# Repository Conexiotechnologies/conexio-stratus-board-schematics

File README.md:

# Conexio Stratus Cellular Board Design
Here you will find the schematic designs for the Conexio Stratus IoT dev kit based on nRF91xx series and the associated shields and the expansion dock.
A detailed description of the pin mapping can be found in each specific board directory.

## nRF9151 Conexio Stratus Pro Series

**Conexio Stratus Pro** is a tiny-yet-powerful development kit for creating cellular-connected electronic projects and products. Powered by the cutting-edge nRF9161 cellular modem from Nordic Semiconductor, Stratus Pro offers unparalleled versatility, reliability, and ease of use, making it the go-to solution for IoT developers worldwide. It is a battery-operated platform, making it ideal for prototyping cellular IoT systems, such as asset tracking, environmental monitoring, smart metering, and even industrial automation.

With LTE-M, NB-IoT, and GPS connectivity packed into a compact form factor, Stratus Pro ensures your devices stay connected in any environment. It enables real-time data transmission and location tracking with minimal power consumption. Future-proof your IoT projects with DECT NR+ readiness, ensuring compatibility with emerging cellular standards for enhanced performance and longevity.

## Built-In Battery Charging, Monitoring and Energy-Harvesting

Thanks to the nPM1300 PMIC and fuel gauge, you can remotely monitor your Stratus Pro’s battery vitals and charging status. Stratus Pro also has built-in charging circuitry that makes it easier to connect to and recharge the Li-Po battery, creating fully energy-autonomous applications.

## Conexio Stratus Pro nRF9151 Pinouts

## Features & Specifications

**MCU**: Nordic nRF9151 Microcontroller 
- ARM Cortex-M33 with 1 MB Flash
- 256 kB RAM
- Pre-programmed MCUBoot bootloader

**Modem**
- Transceiver and baseband
- 3GPP LTE release 14 LTE-M/NB-IoT support
- DECT NR+ ready
- GPS/GNSS receiver
- RF Transceiver for global coverage supporting bands:
- B1, B2, B3, B4, B5, B8, B12, B13, B17, B18, B19, B20, B25, B26, B28, B65 (new), B66, and B85 (new)
- Supports 4FF Nano SIM, optional eSIM, or software SIM

**Included cellular Data**
- 500 MB of cellular data
- 250 SMS messages
- Valid for 10 years, can be reloaded or moved to a new plan
- Service available in 100+ countries (LTE + NB-IoT)

**Power Management IC: Nordic nPM1300**
- 800 mA battery charger
- Dual 200 mA buck DC/DC regulator
- Charging IC: Texas Instruments BQ25185
- Charge inputs: 3 V to 18 V
- Supports Li-ion, Li-Poly, and LiFePO4 battery chemistries

**External Storage**
- 16 KBit I2C EEPROM memory (24CW160T)

**Power**
- Operating range 1.8 to 5.5 V
- External LiPo battery connection (2 Pin JST type)
- Maximum output current: 800 mA
- Output voltages (via headers): 1.8 V, 3.3 V, 5 V (VUSB), VBAT
- SPDT slide switch for turning Stratus Pro on or off
- Quiescent current of entire board < 9 μA

**Onboard sensors**
- Battery fuel gauge enabled by nPM1300
- STMicroelectronics LIS2DH MEMS high-performance 3-axis accelerometer

**I/O**
- USB Type-C, for USB-to-Serial, DFU, and application firmware programming and debugging or battery charging
- 1 x U.FL for LTE-M/NB-IoT antenna
- 1 x U.FL for passive GPS antenna
- Total I/O pinouts: 36
- User I/O: Feather-compatible header, 28 programmable GPIO pins, 2 push buttons (1 reset, 1 programmable), 1 programmable LED
- QWIIC connector for external peripherals
- Supports J-Link and CMSIS-DAP-based programmers
- Onboard 10-pin 0.05 " (1.27 mm) mini SWD/JTAG pin connector

**Size**
- 66.04 mm x 25.40 mm

## Stratus Pro Expansion Dock

Start your product development with our Expansion Dock for Stratus Pro fast and easy. The Expansion Dock offers two QWIIC connectors, two Grove sockets, a mikroBUS™ socket, an nRF7002 Expansion board socket to add Wi-Fi location capabilities, and a SeeedStudio Xiao socket allowing you to create various wireless applications with one host board. It can't get any better than this., working with a Stratus shield requires no soldering and minimal wiring. Just plug the sensors, actuators, or displays into this shield via the standard cables, and focus on coding and application creation.

## Features & Specifications

- 2 x Stratus Pro nRF9151/nRF9161 header sockets.
- 1 x nRF7002EB socket.
- 1 x SeeedStudio Xiao socket.
- 1 x mikro BUS: add-on board standard from Mikroe, allowing connection to over 800+ click boards.
- 2 x Sparkfun Qwiic connector: SparkFun's Qwiic Connect System, allowing to connect over 100+ Qwiic products.
- 2 x Grove I2C connector: Grove is a modular, standardized connector prototyping system by Seeedstudio.
- 1 x 2 Pin JST connector for plugging the solar panel input.
- 1 x 2 Pin JST connector for plugging the lipo battery.
- 1 x Power switch

## Purchase

Conexio Stratus devices and accessories can be purchased directly from our [online store](https://conexiotech.com/shop/).

Please contact [info@conexiotech.com](mailto:info@conexiotech.com) if you would like to arrange help with your manufacturing and custom PCB design based on Stratus Pro platform. 

Copyright (c) 2025 Conexio Technologies, Inc.

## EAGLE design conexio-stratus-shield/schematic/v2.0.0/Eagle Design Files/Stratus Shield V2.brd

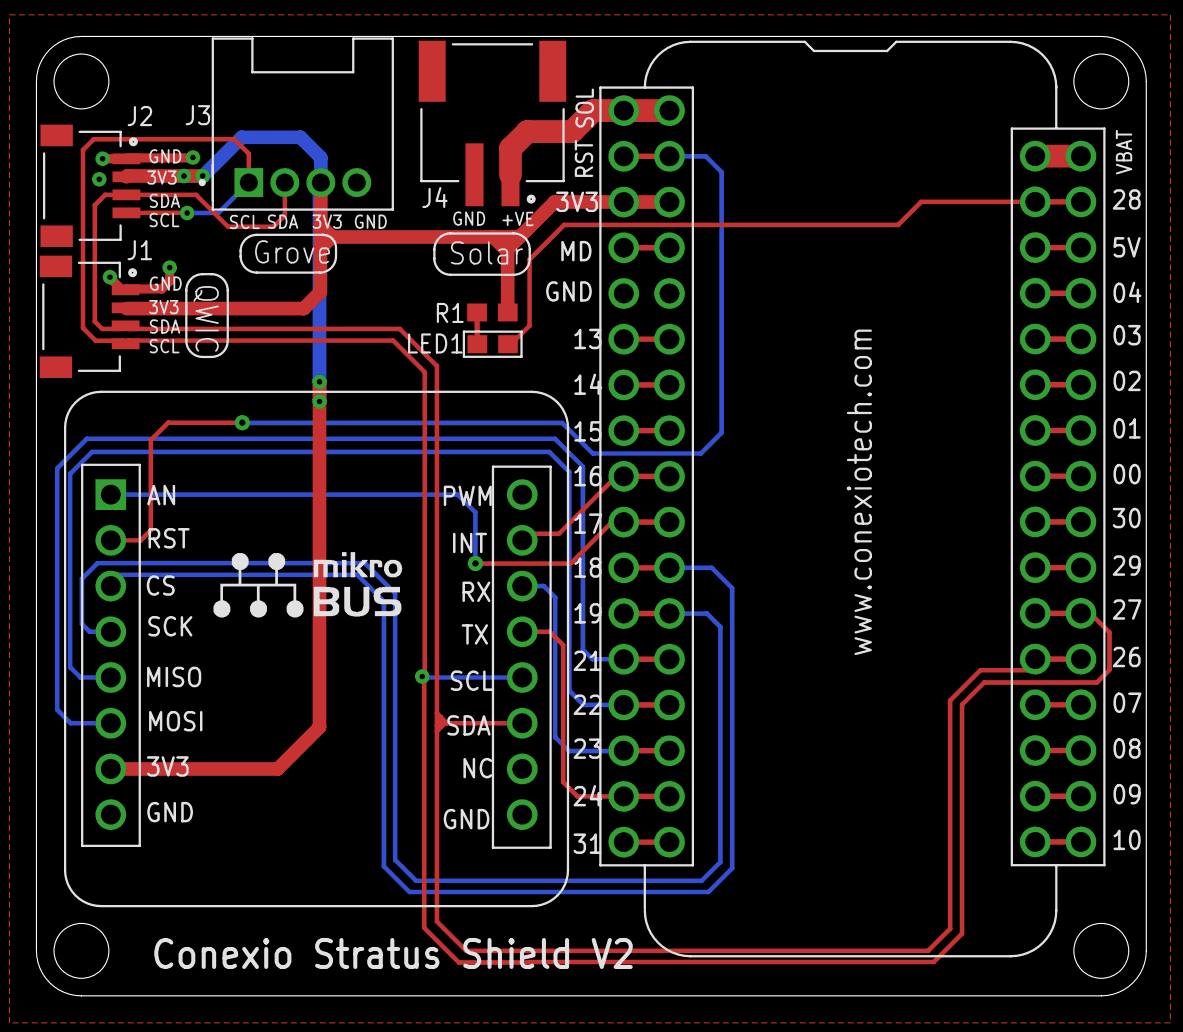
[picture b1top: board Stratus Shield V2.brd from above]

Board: 2 copper layers, 61.7 x 53.3 mm, 12 parts (1 on the bottom side), 34 nets.

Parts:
HEAD1, HEAD4: HEADER_16P; HEADER_16P2.54
HEAD2, HEAD3: SIP-12
J1, J2: PRT-14417; JST_SM04B-SRSS-TB(LF)(SN)
J3: 110990037; HW4-2.0-90D
J4: S2B-PH-SM4-TB(LF)(SN); JST_S2B-PH-SM4-TB(LF)(SN)
J11: MIKROBUS
LED1: BLUE; LED-0603
R1: 330R; R-0603
U$1: ROHS_LOGO_0.18_IN

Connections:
3.3V: HEAD1.3, HEAD4.3, J1.2, J2.2, J3.3, J11.7, R1.1
GND: HEAD1.5, HEAD4.5, J1.1, J1.S1, J1.S2, J2.1, J2.S1, J2.S2, J3.4, J4.2, J4.S1, J4.S2, J11.8, J11.9
MODE/WAKE: HEAD1.4, HEAD4.4
unnamed: LED1.A, R1.2
P0.00/D4: HEAD2.8, HEAD3.8
P0.01/D1: HEAD2.7, HEAD3.7
P0.02/D6: HEAD2.6, HEAD3.6
P0.03/D7: HEAD2.5, HEAD3.5
P0.04/D8: HEAD2.4, HEAD3.4
P0.07/D9: HEAD2.13, HEAD3.13
P0.08/D10: HEAD2.14, HEAD3.14
P0.09/D11: HEAD2.15, HEAD3.15
P0.10/D12: HEAD2.16, HEAD3.16
P0.13/A0: HEAD1.6, HEAD4.6
P0.14/A1: HEAD1.7, HEAD4.7
P0.15/A2: HEAD1.8, HEAD4.8
P0.16/A3: HEAD1.9, HEAD4.9, J11.15
P0.17/A4: HEAD1.10, HEAD4.10, J11.1
P0.18/A5: HEAD1.11, HEAD4.11, J11.3
P0.19/SCK: HEAD1.12, HEAD4.12, J11.4
P0.21/COPI: HEAD1.13, HEAD4.13, J11.6
P0.22/CIPO: HEAD1.14, HEAD4.14, J11.5
P0.23/RX: HEAD1.15, HEAD4.15, J11.14
P0.24/TX: HEAD1.16, HEAD4.16, J11.13
P0.26/SDA: HEAD2.12, HEAD3.12, J1.3, J2.3, J3.2, J11.11
P0.27/SCL: HEAD2.11, HEAD3.11, J1.4, J2.4, J3.1, J11.12
P0.28: HEAD2.2, HEAD3.2, LED1.K
P0.29/D2: HEAD2.10, HEAD3.10
P0.30/D3: HEAD2.9, HEAD3.9
P0.31/NRF_PS_EN: HEAD1.17, HEAD4.17
RST: HEAD1.2, HEAD4.2, J11.2
SOL: HEAD1.1, HEAD4.1, J4.1
VBAT: HEAD2.1, HEAD3.1
VCC-5V: HEAD2.3, HEAD3.3

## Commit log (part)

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2021-08-29 add the component datasheets
2021-09-10 updated readme with stratus details
2021-09-10 add board pinouts diagram
2021-11-07 add conexio stratus shield schematics and license file *released under the CERN Open Hardware Licence Version 2
2024-01-02 add conexio stratus nRF9160 PCB files
2024-01-02 add stratus shield PCB design files
2024-05-13 add Stratus Pro nRF9161 PCB resources
2024-07-16 stratus pro pcb desig files
2025-02-22 add latest board files, pinouts, images
2025-02-22 rename board directories
2025-09-28 add Stratus Pro nRF9151 schematics
2026-06-07 add nRF9151 v1.4 hardware files

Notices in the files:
parts and their libraries:
SparkFun-Aesthetics: Licensing: Creative Commons ShareAlike 4.0 International - https://creativecommons.org/licenses/by-sa/4.0
